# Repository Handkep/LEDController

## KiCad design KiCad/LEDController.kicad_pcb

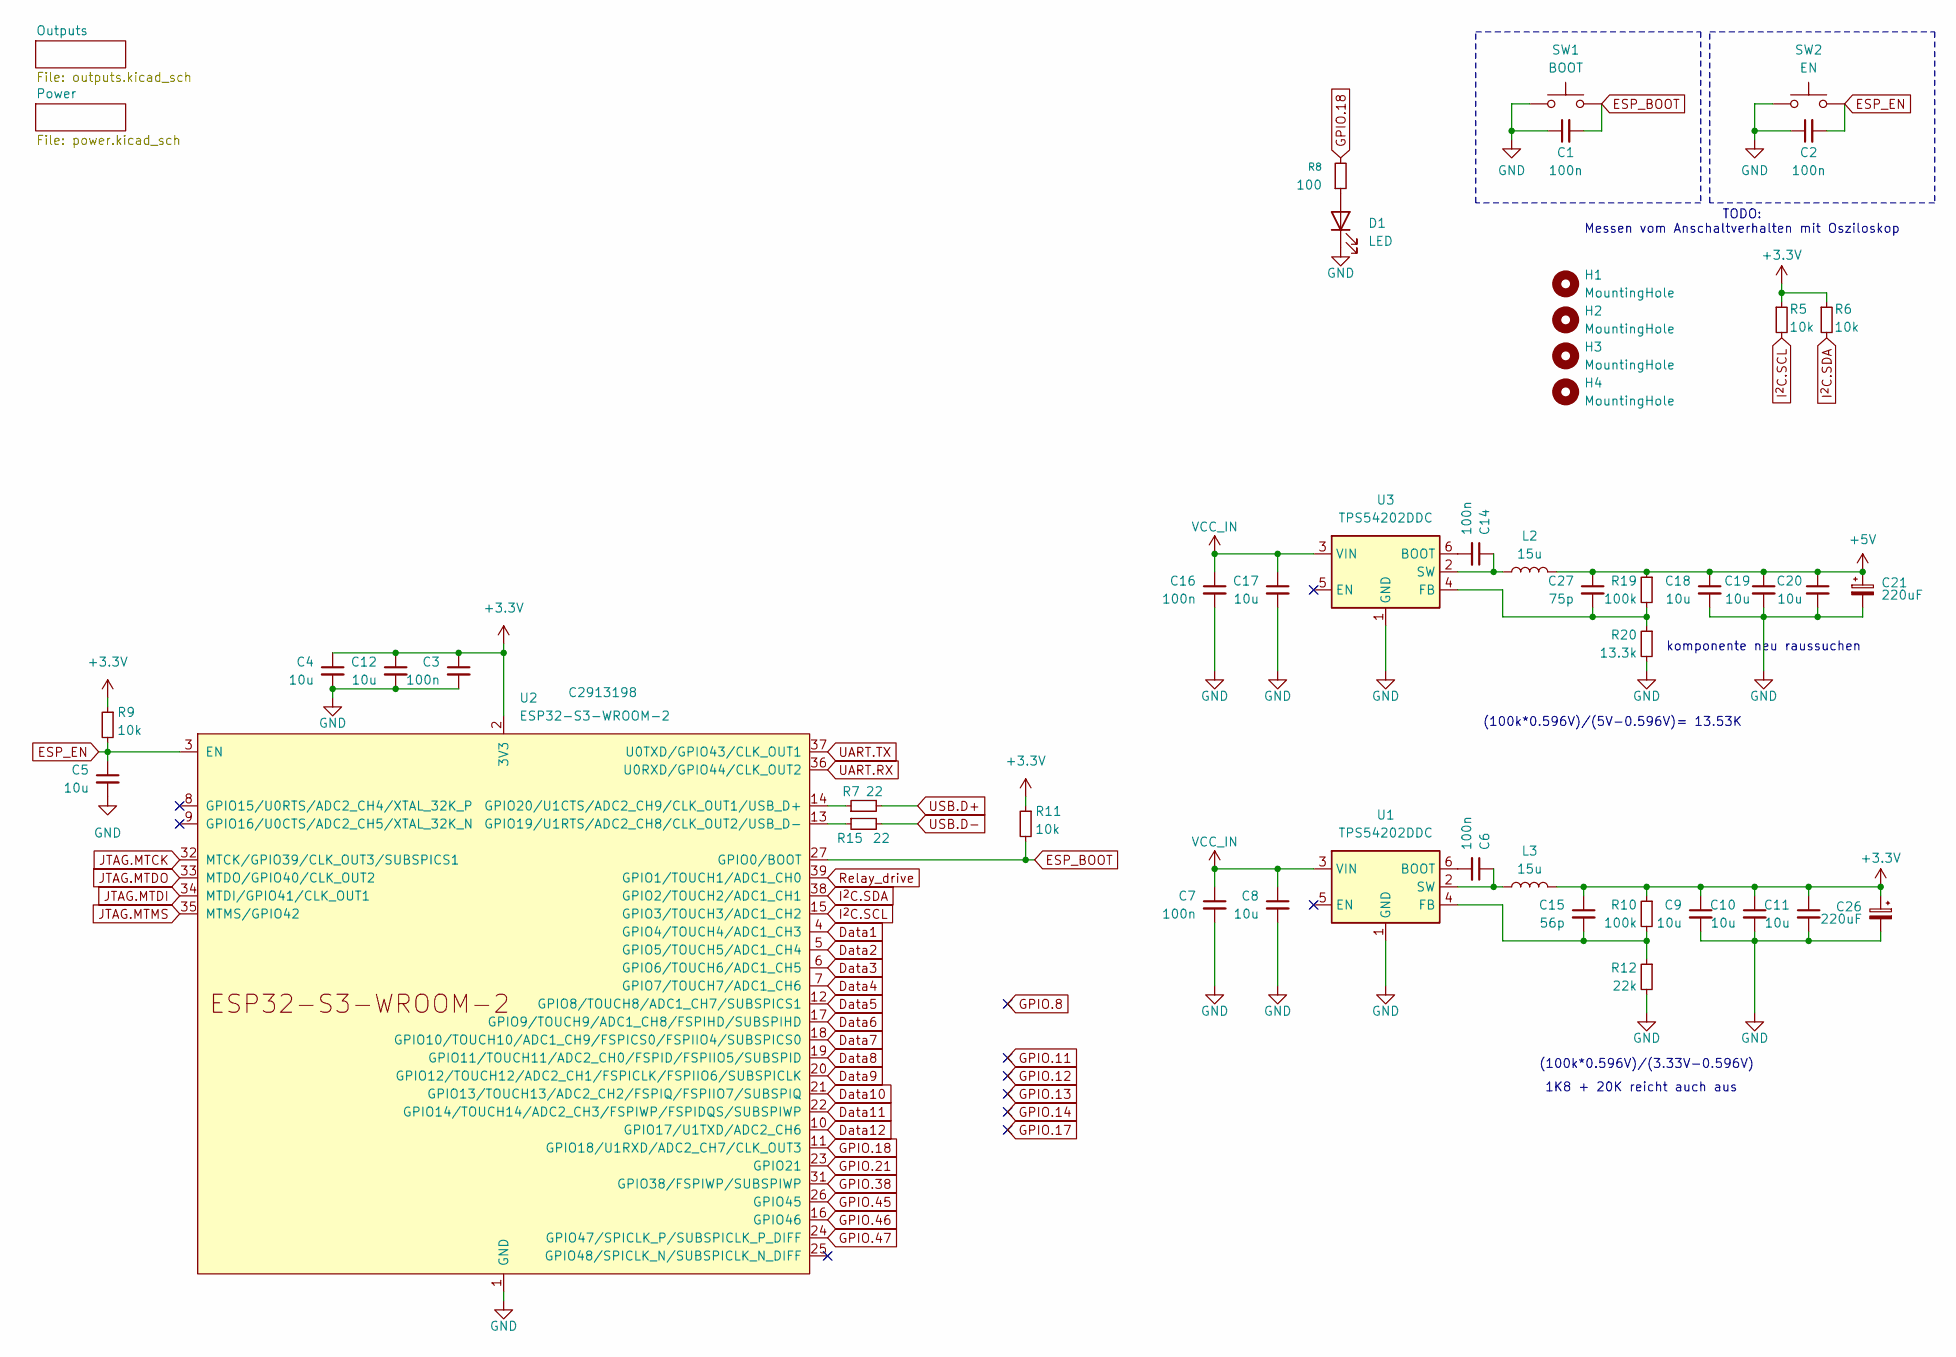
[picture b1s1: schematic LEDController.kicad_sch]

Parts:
C1, C2, C3, C6, C7, C14, C16: 100n; C_0805_2012Metric_Pad1.18x1.45mm_HandSolder; LCSC C5137467
C4, C5, C8, C9, C10, C11, C12, C17, C18, C19, C20: 10u; C_0805_2012Metric_Pad1.18x1.45mm_HandSolder; LCSC C33546007
C15: 56p; C_0805_2012Metric_Pad1.18x1.45mm_HandSolder
C21, C26: 220uF; CP_Radial_D8.0mm_P3.50mm; LCSC C107639
C27: 75p; C_0805_2012Metric_Pad1.18x1.45mm_HandSolder
D1: LED; LED_0603_1608Metric_Pad1.05x0.95mm_HandSolder; LCSC C7496818
H1, H2, H3, H4: MountingHole; MountingHole_3.2mm_M3
L2, L3: 15u; L_APV_APH0630; LCSC C5349699
R5, R6, R9, R11: 10k; R_0805_2012Metric_Pad1.20x1.40mm_HandSolder; LCSC C2930231
R7, R15: 22; R_0805_2012Metric_Pad1.20x1.40mm_HandSolder
R8: 100; R_0805_2012Metric_Pad1.20x1.40mm_HandSolder; LCSC C2907294
R10, R19: 100k; R_0805_2012Metric_Pad1.20x1.40mm_HandSolder; LCSC C3017875
R12: 22k; R_0805_2012Metric_Pad1.20x1.40mm_HandSolder; LCSC C2907015
R20: 13.3k; R_0805_2012Metric_Pad1.20x1.40mm_HandSolder; LCSC C3017875
SW1: BOOT; SHOU HAN TS342A2P-WZ; LCSC C557591
SW2: EN; SHOU HAN TS342A2P-WZ; LCSC C557591
U1, U3: TPS54202DDC; SOT-23-6; LCSC C191884
U2: ESP32-S3-WROOM-2; LCSC C2913198

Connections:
+3.3V: C3.1, C4.1, C9.1, C10.1, C11.1, C12.1, C15.1, C26.1, L3.2, R5.1, R6.1, R9.1, R10.1, R11.1, U2.2 (3V3); also elsewhere on the board
+5V: C18.1, C19.1, C20.1, C21.1, C27.1, L2.2, R19.1; also elsewhere on the board
Data1: U2.4 (GPIO4/TOUCH4/ADC1_CH3); also elsewhere on the board
Data2: U2.5 (GPIO5/TOUCH5/ADC1_CH4); also elsewhere on the board
Data3: U2.6 (GPIO6/TOUCH6/ADC1_CH5); also elsewhere on the board
Data4: U2.7 (GPIO7/TOUCH7/ADC1_CH6); also elsewhere on the board
Data5: U2.12 (GPIO8/TOUCH8/ADC1_CH7/SUBSPICS1); also elsewhere on the board
Data6: U2.17 (GPIO9/TOUCH9/ADC1_CH8/FSPIHD/SUBSPIHD); also elsewhere on the board
Data7: U2.18 (GPIO10/TOUCH10/ADC1_CH9/FSPICS0/FSPIIO4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); also elsewhere on the board
Data8: U2.19 (GPIO11/TOUCH11/ADC2_CH0/FSPID/FSPIIO5/S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); also elsewhere on the board
Data9: U2.20 (GPIO12/TOUCH12/ADC2_CH1/FSPICLK/FSPIIO6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); also elsewhere on the board
Data10: U2.21 (GPIO13/TOUCH13/ADC2_CH2/FSPIQ/FSPIIO7/S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); also elsewhere on the board
Data11: U2.22 (GPIO14/TOUCH14/ADC2_CH3/FSPIWP/FSPIDQS/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)
Data12: U2.10 (GPIO17/U1TXD/ADC2_CH6)
ESP_BOOT: C1.2, R11.2, SW1.2, U2.27 (GPIO0/BOOT)
ESP_EN: C2.2, C5.1, R9.2, SW2.2, U2.3 (EN)
GND: C1.1, C2.1, C3.2, C4.2, C5.2, C7.2, C8.2, C9.2, C10.2, C11.2, C12.2, C16.2, C17.2, C18.2, C19.2, C20.2, C21.2, C26.2, D1.1 (K), R12.2, R20.2, SW1.1, SW2.1, U1.1 (GND), U2.1 (GND), U2.40 (GND), U2.41 (GND), U3.1 (GND); also elsewhere on the board
GPIO.18: R8.2, U2.11 (GPIO18/U1RXD/ADC2_CH7/CLK_OUT3); also elsewhere on the board
GPIO.21: U2.23 (GPIO21); also elsewhere on the board
GPIO.38: U2.31 (GPIO38/FSPIWP/SUBSPIWP); also elsewhere on the board
GPIO.45: U2.26 (GPIO45); also elsewhere on the board
GPIO.46: U2.16 (GPIO46); also elsewhere on the board
GPIO.47: U2.24 (GPIO47/SPICLK_P/SUBSPICLK_P_DIFF); also elsewhere on the board
I^{2}C.SCL: R5.2, U2.15 (GPIO3/TOUCH3/ADC1_CH2)
I^{2}C.SDA: R6.2, U2.38 (GPIO2/TOUCH2/ADC1_CH1)
JTAG.MTCK: U2.32 (MTCK/GPIO39/CLK_OUT3/SUBSPICS1); also elsewhere on the board
JTAG.MTDI: U2.34 (MTDI/GPIO41/CLK_OUT1); also elsewhere on the board
JTAG.MTDO: U2.33 (MTDO/GPIO40/CLK_OUT2); also elsewhere on the board
JTAG.MTMS: U2.35 (MTMS/GPIO42); also elsewhere on the board
unnamed: D1.2 (A), R8.1
unnamed: C6.2, U1.6 (BOOT)
unnamed: C15.2, R10.2, R12.1, U1.4 (FB)
unnamed: C6.1, L3.1, U1.2 (SW)
unnamed: R15.1, U2.13 (GPIO19/U1RTS/ADC2_CH8/CLK_OUT2/USB_D-)
unnamed: R7.1, U2.14 (GPIO20/U1CTS/ADC2_CH9/CLK_OUT1/USB_D+)
unnamed: C14.2, U3.6 (BOOT)
unnamed: C27.2, R19.2, R20.1, U3.4 (FB)
unnamed: C14.1, L2.1, U3.2 (SW)
Relay_drive: U2.39 (GPIO1/TOUCH1/ADC1_CH0); also elsewhere on the board
UART.RX: U2.36 (U0RXD/GPIO44/CLK_OUT2); also elsewhere on the board
UART.TX: U2.37 (U0TXD/GPIO43/CLK_OUT1); also elsewhere on the board
USB.D+: R7.2; also elsewhere on the board
USB.D-: R15.2; also elsewhere on the board
VCC_IN: C7.1, C8.1, C16.1, C17.1, U1.3 (VIN), U3.3 (VIN); also elsewhere on the board

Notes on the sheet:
(100k*0.596V)/(5V-0.596V)= 13.53K
komponente neu raussuchen
(100k*0.596V)/(3.33V-0.596V)
1K8 + 20K reicht auch aus
TODO: Messen vom Anschaltverhalten mit Osziloskop

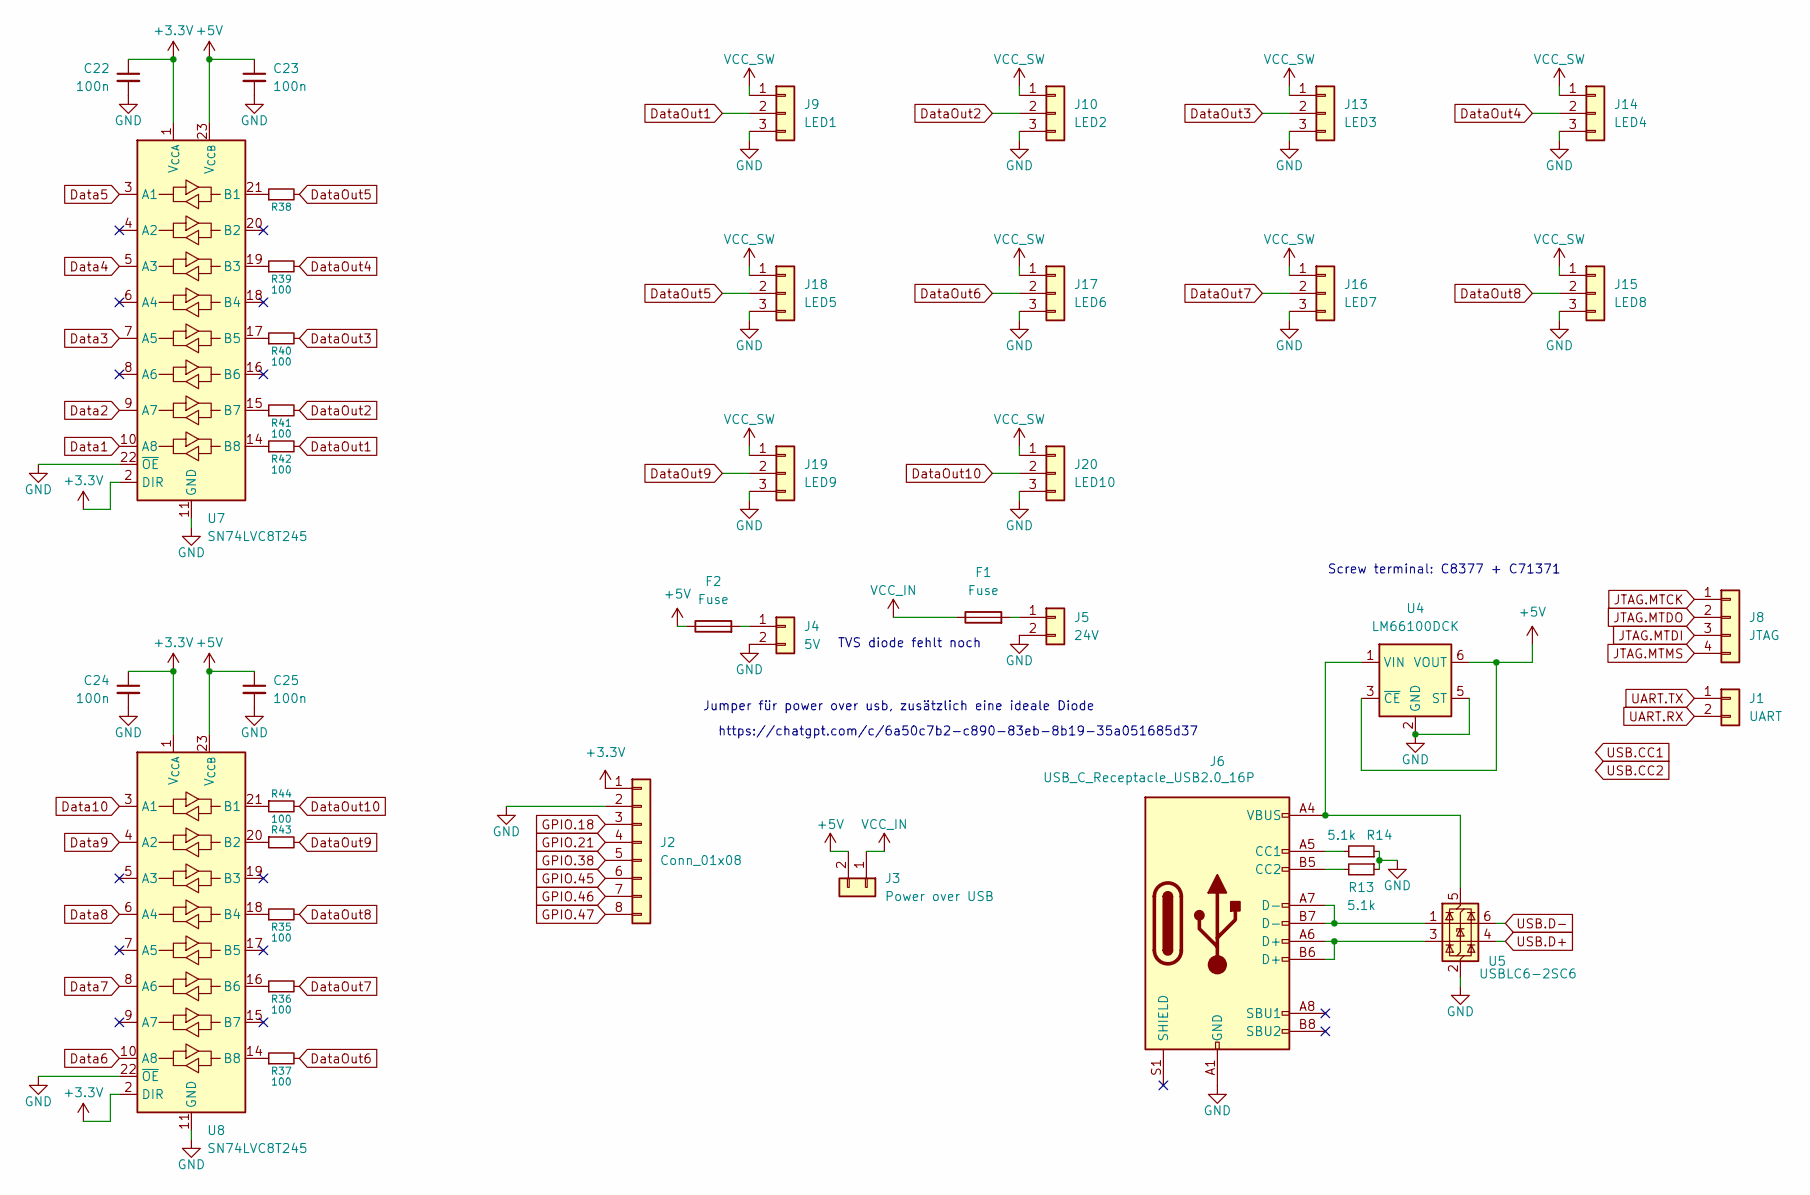
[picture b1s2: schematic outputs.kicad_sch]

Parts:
C22, C23, C24, C25: 100n; C_0805_2012Metric_Pad1.18x1.45mm_HandSolder; LCSC C5137467
F1, F2: Fuse; Fuseholder_Blade_Mini_Keystone_3568; LCSC C19727305
J1: UART; PinHeader_1x02_P2.54mm_Vertical
J2: Conn_01x08; PinHeader_1x08_P2.54mm_Vertical
J3: Power over USB; PinHeader_1x02_P2.54mm_Vertical
J4: 5V; CONN-TH_HB9500M-9.5-2P; LCSC C601239
J5: 24V; CONN-TH_HB9500M-9.5-2P; LCSC C601239
J6: USB_C_Receptacle_USB2.0_16P; USB_C_Receptacle_GCT_USB4105-xx-A_16P_TopMnt_Horizontal; LCSC C2765186
J8: JTAG; PinHeader_1x04_P2.54mm_Vertical
J9: LED1; CONN-TH_3P-P5.08_WJ2EDGRC-5.08-3P; LCSC C8377
J10: LED2; CONN-TH_3P-P5.08_WJ2EDGRC-5.08-3P; LCSC C8377
J13: LED3; CONN-TH_3P-P5.08_WJ2EDGRC-5.08-3P; LCSC C8377
J14: LED4; CONN-TH_3P-P5.08_WJ2EDGRC-5.08-3P; LCSC C8377
J15: LED8; CONN-TH_3P-P5.08_WJ2EDGRC-5.08-3P; LCSC C8377
J16: LED7; CONN-TH_3P-P5.08_WJ2EDGRC-5.08-3P; LCSC C8377
J17: LED6; CONN-TH_3P-P5.08_WJ2EDGRC-5.08-3P; LCSC C8377
J18: LED5; CONN-TH_3P-P5.08_WJ2EDGRC-5.08-3P; LCSC C8377
J19: LED9; CONN-TH_3P-P5.08_WJ2EDGRC-5.08-3P; LCSC C8377
J20: LED10; CONN-TH_3P-P5.08_WJ2EDGRC-5.08-3P; LCSC C8377
R13, R14: 5.1k; R_0805_2012Metric_Pad1.20x1.40mm_HandSolder; LCSC C2930296
R35, R36, R37, R38, R39, R40, R41, R42, R43, R44: 100; R_0805_2012Metric_Pad1.20x1.40mm_HandSolder; LCSC C2907294
U4: LM66100DCK; SOT-363_SC-70-6; LCSC C2869734
U5: USBLC6-2SC6; SOT-23-6; LCSC C21713975
U7, U8: SN74LVC8T245; TSSOP-24_4.4x7.8mm_P0.65mm; LCSC C27643

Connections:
+3.3V: C22.1, C24.1, J2.1, U7.1 (V_{CCA}), U7.2 (DIR), U8.1 (V_{CCA}), U8.2 (DIR); also elsewhere on the board
+5V: C23.1, C25.1, F2.1, J3.2, U4.3 (~CE), U4.6 (VOUT), U7.23 (V_{CCB}), U7.24 (V_{CCB}), U8.23 (V_{CCB}), U8.24 (V_{CCB}); also elsewhere on the board
Data1: U7.10 (A8); also elsewhere on the board
Data2: U7.9 (A7); also elsewhere on the board
Data3: U7.7 (A5); also elsewhere on the board
Data4: U7.5 (A3); also elsewhere on the board
Data5: U7.3 (A1); also elsewhere on the board
Data6: U8.10 (A8); also elsewhere on the board
Data7: U8.8 (A6); also elsewhere on the board
Data8: U8.6 (A4); also elsewhere on the board
Data9: U8.4 (A2); also elsewhere on the board
Data10: U8.3 (A1); also elsewhere on the board
DataOut1: J9.2, R42.2
DataOut2: J10.2, R41.2
DataOut3: J13.2, R40.2
DataOut4: J14.2, R39.2
DataOut5: J18.2, R38.2
DataOut6: J17.2, R37.2
DataOut7: J16.2, R36.2
DataOut8: J15.2, R35.2
DataOut9: J19.2, R43.2
DataOut10: J20.2, R44.2
GND: C22.2, C23.2, C24.2, C25.2, J2.2, J4.2, J5.2, J6.A1 (GND), J6.A12 (GND), J6.B1 (GND), J6.B12 (GND), J9.3, J10.3, J13.3, J14.3, J15.3, J16.3, J17.3, J18.3, J19.3, J20.3, R13.1, R14.1, U4.2 (GND), U4.5 (ST), U5.2 (GND), U7.11 (GND), U7.12 (GND), U7.13 (GND), U7.22 (~OE), U8.11 (GND), U8.12 (GND), U8.13 (GND), U8.22 (~OE); also elsewhere on the board
GPIO.18: J2.3; also elsewhere on the board
GPIO.21: J2.4; also elsewhere on the board
GPIO.38: J2.5; also elsewhere on the board
GPIO.45: J2.6; also elsewhere on the board
GPIO.46: J2.7; also elsewhere on the board
GPIO.47: J2.8; also elsewhere on the board
JTAG.MTCK: J8.1; also elsewhere on the board
JTAG.MTDI: J8.3; also elsewhere on the board
JTAG.MTDO: J8.2; also elsewhere on the board
JTAG.MTMS: J8.4; also elsewhere on the board
unnamed: F2.2, J4.1
unnamed: F1.2, J5.1
unnamed: J6.A5 (CC1), R14.2
unnamed: J6.B5 (CC2), R13.2
unnamed: J6.A6 (D+), J6.B6 (D+), U5.3 (I/O2)
unnamed: J6.A7 (D-), J6.B7 (D-), U5.1 (I/O1)
unnamed: J6.A4 (VBUS), J6.A9 (VBUS), J6.B4 (VBUS), J6.B9 (VBUS), U4.1 (VIN), U5.5 (VBUS)
unnamed: R38.1, U7.21 (B1)
unnamed: R39.1, U7.19 (B3)
unnamed: R40.1, U7.17 (B5)
unnamed: R41.1, U7.15 (B7)
unnamed: R42.1, U7.14 (B8)
unnamed: R44.1, U8.21 (B1)
unnamed: R43.1, U8.20 (B2)
unnamed: R35.1, U8.18 (B4)
unnamed: R36.1, U8.16 (B6)
unnamed: R37.1, U8.14 (B8)
UART.RX: J1.2; also elsewhere on the board
UART.TX: J1.1; also elsewhere on the board
USB.D+: U5.4 (I/O2); also elsewhere on the board
USB.D-: U5.6 (I/O1); also elsewhere on the board
VCC_IN: F1.1, J3.1; also elsewhere on the board
VCC_SW: J9.1, J10.1, J13.1, J14.1, J15.1, J16.1, J17.1, J18.1, J19.1, J20.1; also elsewhere on the board

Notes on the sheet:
TVS diode fehlt noch
https://chatgpt.com/c/6a50c7b2-c890-83eb-8b19-35a051685d37
Jumper für power over usb, zusätzlich eine ideale Diode
Screw terminal: C8377 + C71371

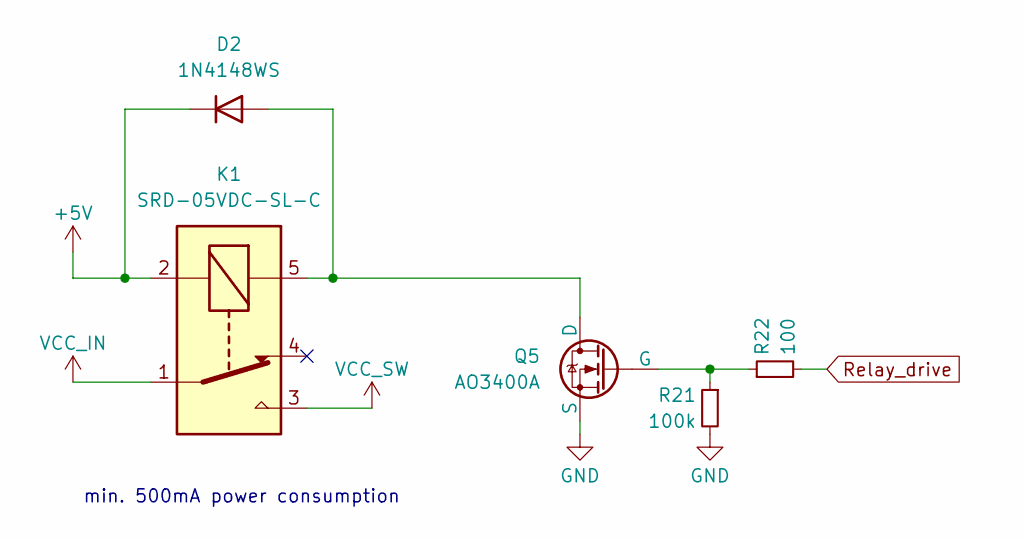
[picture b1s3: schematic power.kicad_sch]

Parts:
D2: 1N4148WS; D_SOD-323; LCSC C917030
K1: SRD-05VDC-SL-C; Relay_SPDT_SANYOU_SRD_Series_Form_C; LCSC C35449
Q5: AO3400A; SOT-23; LCSC C20917
R21: 100k; R_0805_2012Metric_Pad1.20x1.40mm_HandSolder; LCSC C3017875
R22: 100; R_0805_2012Metric_Pad1.20x1.40mm_HandSolder; LCSC C2907294

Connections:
+5V: D2.1 (K), K1.2; also elsewhere on the board
GND: Q5.3 (S), R21.2; also elsewhere on the board
unnamed: D2.2 (A), K1.5, Q5.1 (D)
unnamed: Q5.2 (G), R21.1, R22.1
Relay_drive: R22.2; also elsewhere on the board
VCC_IN: K1.1; also elsewhere on the board
VCC_SW: K1.3; also elsewhere on the board

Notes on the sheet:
min. 500mA power consumption

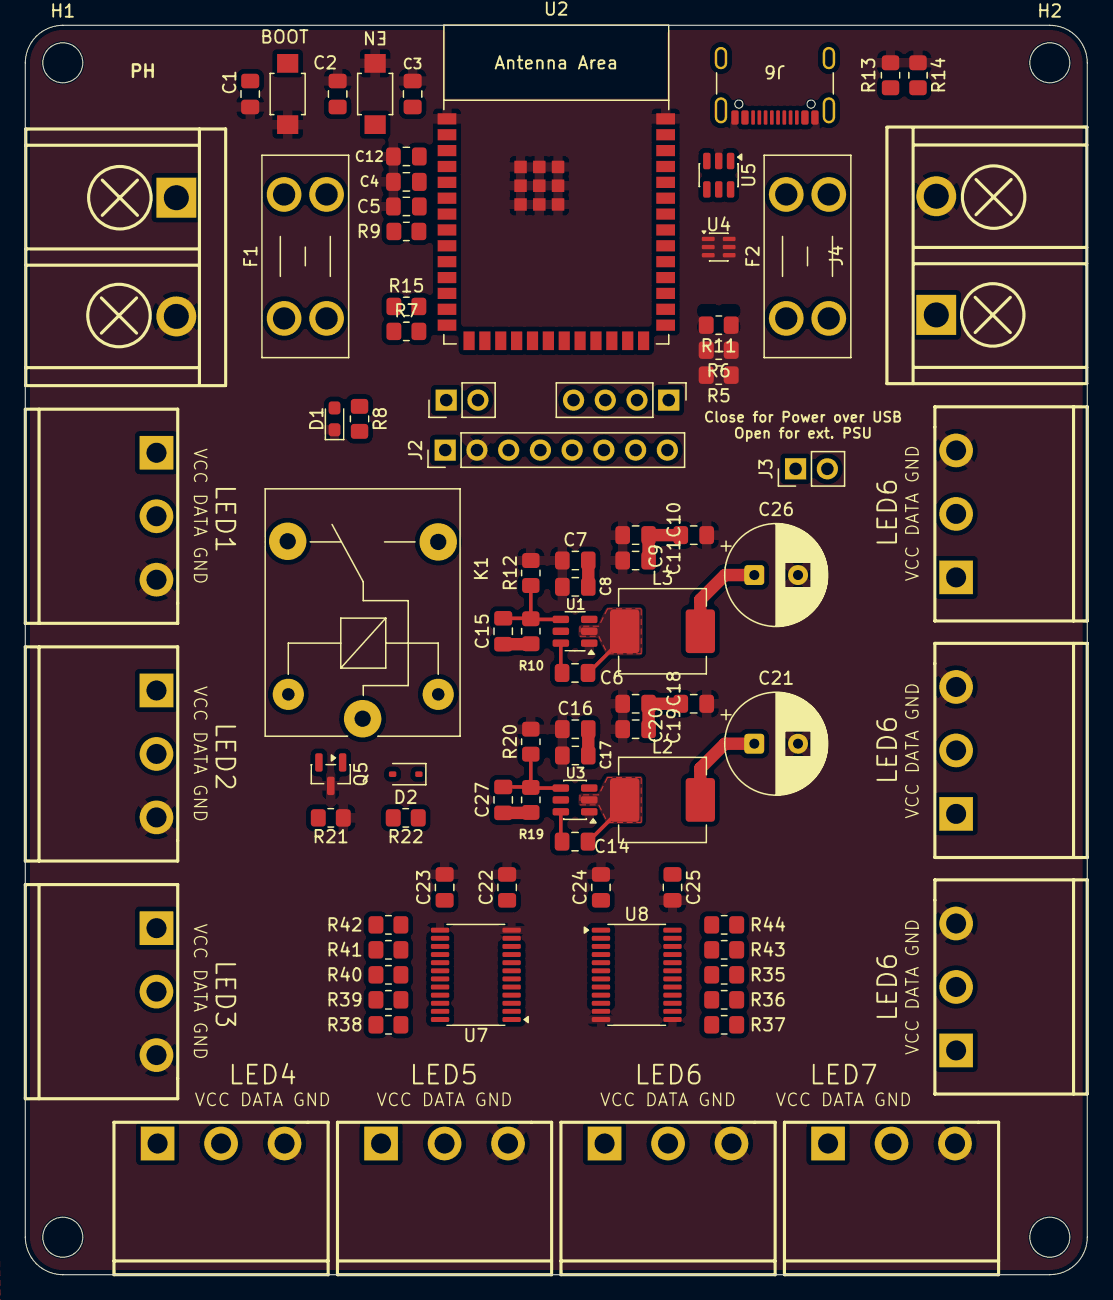
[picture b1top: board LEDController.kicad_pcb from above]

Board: 4 copper layers, 85.0 x 100.0 mm, 89 parts (0 on the bottom side), 72 nets.

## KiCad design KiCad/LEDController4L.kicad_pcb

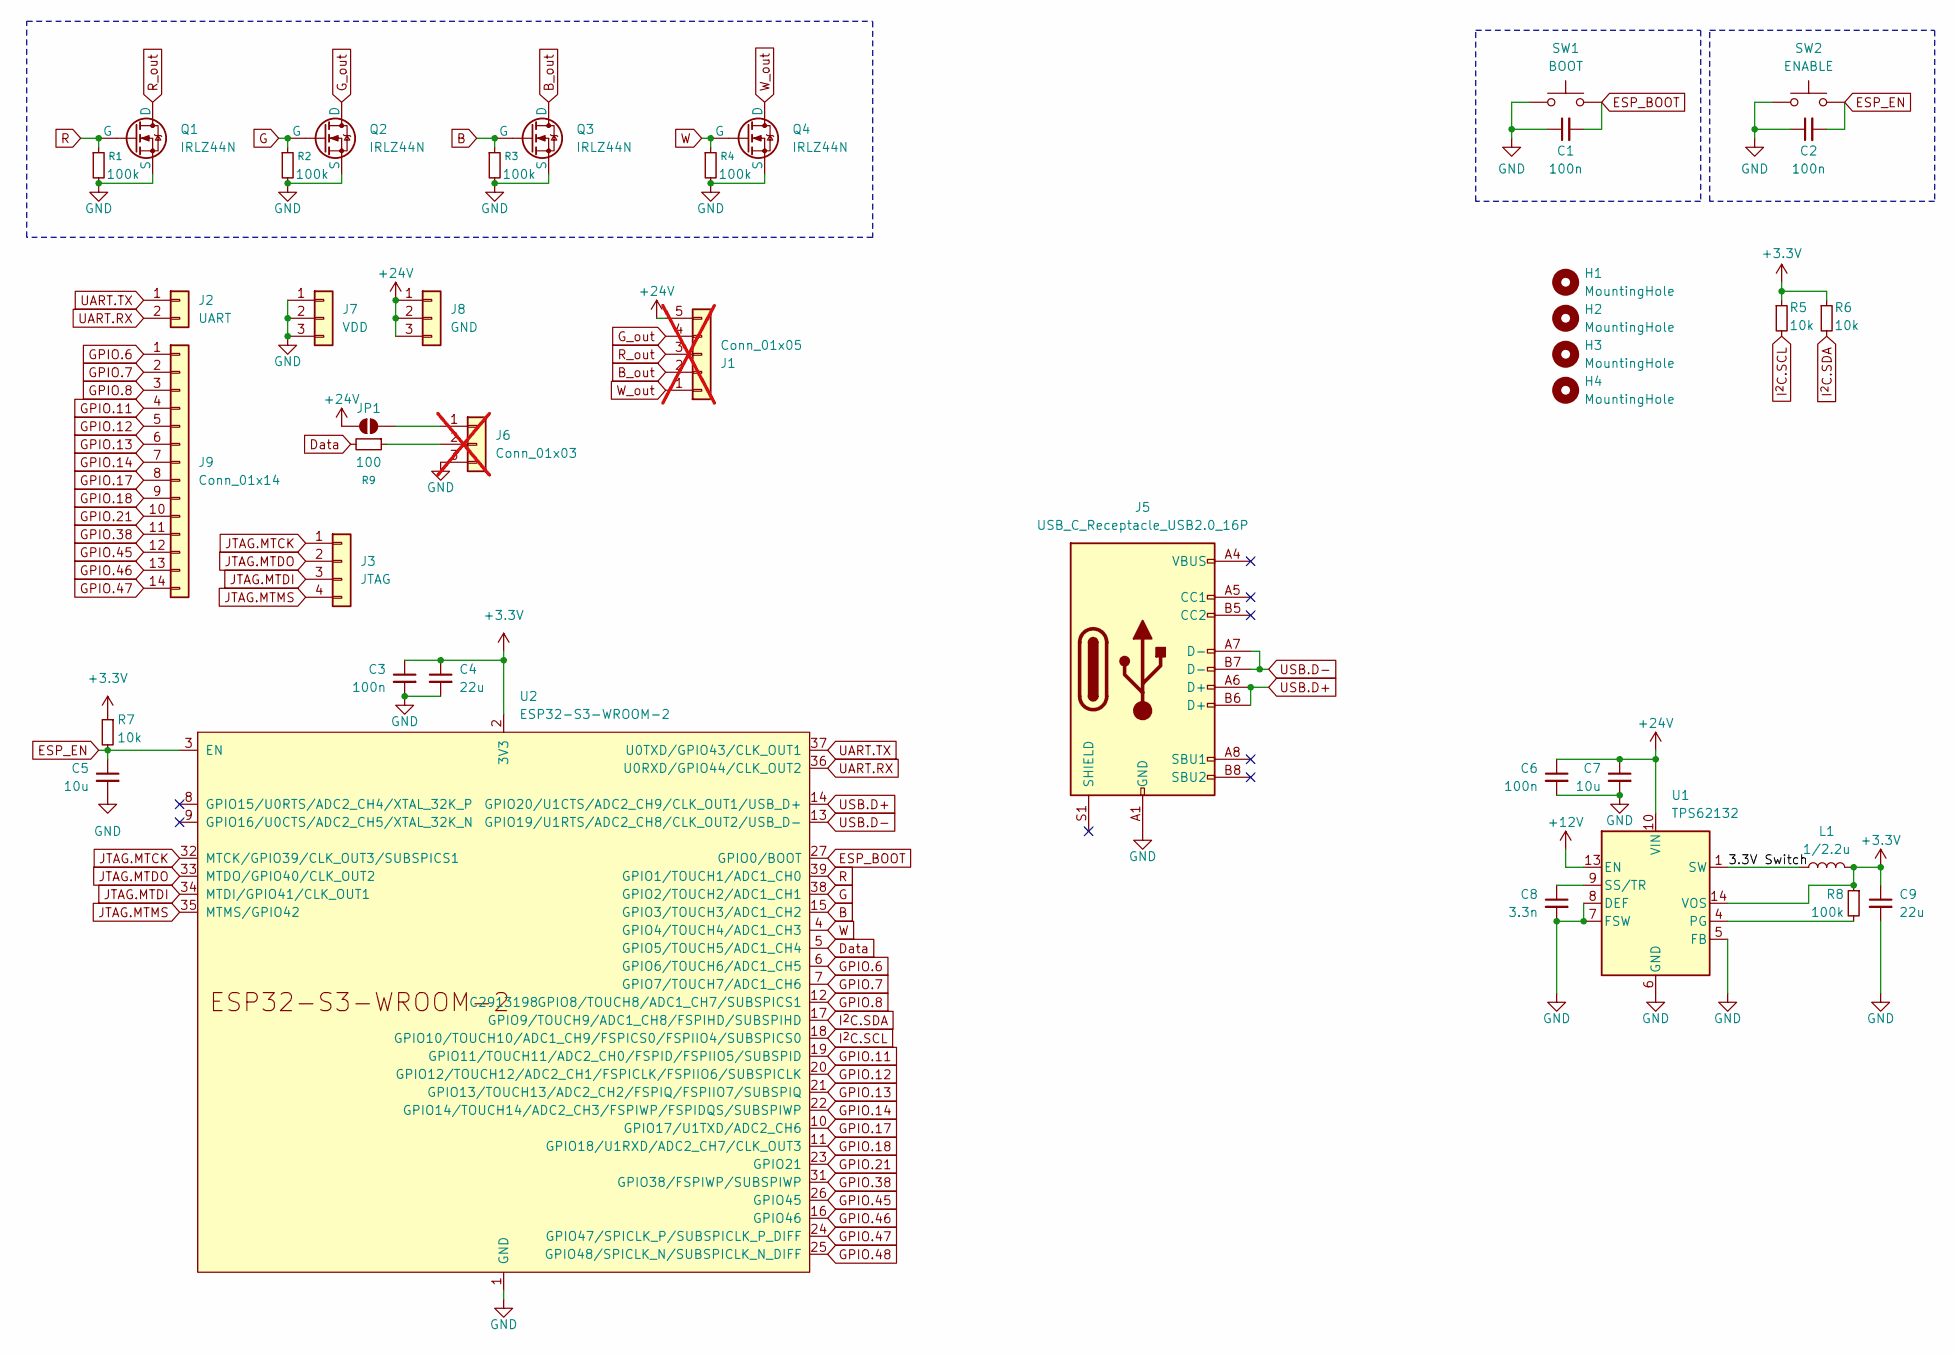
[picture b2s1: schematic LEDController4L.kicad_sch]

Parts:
C1, C2, C3, C6: 100n; C_0805_2012Metric_Pad1.18x1.45mm_HandSolder
C4, C9: 22u; C_0805_2012Metric_Pad1.18x1.45mm_HandSolder
C5, C7: 10u; C_1210_3225Metric_Pad1.33x2.70mm_HandSolder
C8: 3.3n; C_0805_2012Metric_Pad1.18x1.45mm_HandSolder
H1, H2, H3, H4: MountingHole; MountingHole_3.2mm_M3
J1: Conn_01x05; JST_XH_B5B-XH-A_1x05_P2.50mm_Vertical; not fitted
J2: UART; PinHeader_1x02_P2.54mm_Vertical
J3: JTAG; PinHeader_1x04_P2.54mm_Vertical
J5: USB_C_Receptacle_USB2.0_16P; USB_C_Receptacle_GCT_USB4105-xx-A_16P_TopMnt_Horizontal; LCSC C2765186
J6: Conn_01x03; JST_XH_B3B-XH-A_1x03_P2.50mm_Vertical; not fitted
J7: VDD; TerminalBlock_Phoenix_MKDS-1,5-3-5.08_1x03_P5.08mm_Horizont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
J8: GND; TerminalBlock_Phoenix_MKDS-1,5-3-5.08_1x03_P5.08mm_Horizont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
J9: Conn_01x14; PinHeader_1x14_P2.54mm_Vertical
JP1: SolderJumper_2_Open; SolderJumper-2_P1.3mm_Open_RoundedPad1.0x1.5mm
L1: 1/2.2u; L_APV_ANR4026
Q1, Q2, Q3, Q4: IRLZ44N; TO-220-3_Vertical; LCSC C42370423
R1, R2, R3, R4, R8: 100k; R_0805_2012Metric_Pad1.20x1.40mm_HandSolder; LCSC C3017875
R5, R6, R7: 10k; R_0805_2012Metric_Pad1.20x1.40mm_HandSolder; LCSC C2930231
R9: 100; R_0805_2012Metric_Pad1.20x1.40mm_HandSolder; LCSC C2907294
SW1: BOOT; SHOU HAN TS342A2P-WZ; LCSC C557591
SW2: ENABLE; SHOU HAN TS342A2P-WZ; LCSC C557591
U1: TPS62132; VQFN-16-1EP_3x3mm_P0.5mm_EP1.68x1.68mm_ThermalVias; LCSC C81563
U2: ESP32-S3-WROOM-2; LCSC C2913198

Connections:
+3.3V: C3.1, C4.1, C9.1, L1.2, R5.1, R6.1, R7.1, R8.1, U1.14 (VOS), U2.2 (3V3)
+12V: U1.13 (EN)
+24V: C6.1, C7.1, J1.5, J8.1, J8.2, J8.3, JP1.1 (A), U1.10 (VIN), U1.11 (VIN), U1.12 (VIN)
/3.3V Switch: L1.1, U1.1 (SW), U1.2 (SW), U1.3 (SW)
B: Q3.2 (G), R3.1, U2.15 (GPIO3/TOUCH3/ADC1_CH2)
B_out: J1.2, Q3.1 (D)
Data: R9.2, U2.5 (GPIO5/TOUCH5/ADC1_CH4)
ESP_BOOT: C1.2, SW1.2, U2.27 (GPIO0/BOOT)
ESP_EN: C2.2, C5.1, R7.2, SW2.2, U2.3 (EN)
G: Q2.2 (G), R2.1, U2.38 (GPIO2/TOUCH2/ADC1_CH1)
GND: C1.1, C2.1, C3.2, C4.2, C5.2, C6.2, C7.2, C8.2, C9.2, J5.A1 (GND), J5.A12 (GND), J5.B1 (GND), J5.B12 (GND), J6.3, J7.1, J7.2, J7.3, Q1.3 (S), Q2.3 (S), Q3.3 (S), Q4.3 (S), R1.2, R2.2, R3.2, R4.2, SW1.1, SW2.1, U1.5 (FB), U1.6 (GND), U1.7 (FSW), U1.8 (DEF), U1.15 (GND), U1.16 (GND), U1.17 (GND), U2.1 (GND), U2.40 (GND), U2.41 (GND)
GPIO.6: J9.1, U2.6 (GPIO6/TOUCH6/ADC1_CH5)
GPIO.7: J9.2, U2.7 (GPIO7/TOUCH7/ADC1_CH6)
GPIO.8: J9.3, U2.12 (GPIO8/TOUCH8/ADC1_CH7/SUBSPICS1)
GPIO.11: J9.4, U2.19 (GPIO11/TOUCH11/ADC2_CH0/FSPID/FSPIIO5/S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)
GPIO.12: J9.5, U2.20 (GPIO12/TOUCH12/ADC2_CH1/FSPICLK/FSPIIO6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)
GPIO.13: J9.6, U2.21 (GPIO13/TOUCH13/ADC2_CH2/FSPIQ/FSPIIO7/S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)
GPIO.14: J9.7, U2.22 (GPIO14/TOUCH14/ADC2_CH3/FSPIWP/FSPIDQS/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)
GPIO.17: J9.8, U2.10 (GPIO17/U1TXD/ADC2_CH6)
GPIO.18: J9.9, U2.11 (GPIO18/U1RXD/ADC2_CH7/CLK_OUT3)
GPIO.21: J9.10, U2.23 (GPIO21)
GPIO.38: J9.11, U2.31 (GPIO38/FSPIWP/SUBSPIWP)
GPIO.45: J9.12, U2.26 (GPIO45)
GPIO.46: J9.13, U2.16 (GPIO46)
GPIO.47: J9.14, U2.24 (GPIO47/SPICLK_P/SUBSPICLK_P_DIFF)
GPIO.48: U2.25 (GPIO48/SPICLK_N/SUBSPICLK_N_DIFF)
G_out: J1.4, Q2.1 (D)
I^{2}C.SCL: R5.2, U2.18 (GPIO10/TOUCH10/ADC1_CH9/FSPICS0/FSPIIO4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)
I^{2}C.SDA: R6.2, U2.17 (GPIO9/TOUCH9/ADC1_CH8/FSPIHD/SUBSPIHD)
JTAG.MTCK: J3.1, U2.32 (MTCK/GPIO39/CLK_OUT3/SUBSPICS1)
JTAG.MTDI: J3.3, U2.34 (MTDI/GPIO41/CLK_OUT1)
JTAG.MTDO: J3.2, U2.33 (MTDO/GPIO40/CLK_OUT2)
JTAG.MTMS: J3.4, U2.35 (MTMS/GPIO42)
unnamed: J6.1, JP1.2 (B)
unnamed: J6.2, R9.1
unnamed: R8.2, U1.4 (PG)
unnamed: C8.1, U1.9 (SS/TR)
R: Q1.2 (G), R1.1, U2.39 (GPIO1/TOUCH1/ADC1_CH0)
R_out: J1.3, Q1.1 (D)
UART.RX: J2.2, U2.36 (U0RXD/GPIO44/CLK_OUT2)
UART.TX: J2.1, U2.37 (U0TXD/GPIO43/CLK_OUT1)
USB.D+: J5.A6 (D+), J5.B6 (D+), U2.14 (GPIO20/U1CTS/ADC2_CH9/CLK_OUT1/USB_D+)
USB.D-: J5.A7 (D-), J5.B7 (D-), U2.13 (GPIO19/U1RTS/ADC2_CH8/CLK_OUT2/USB_D-)
W: Q4.2 (G), R4.1, U2.4 (GPIO4/TOUCH4/ADC1_CH3)
W_out: J1.1, Q4.1 (D)

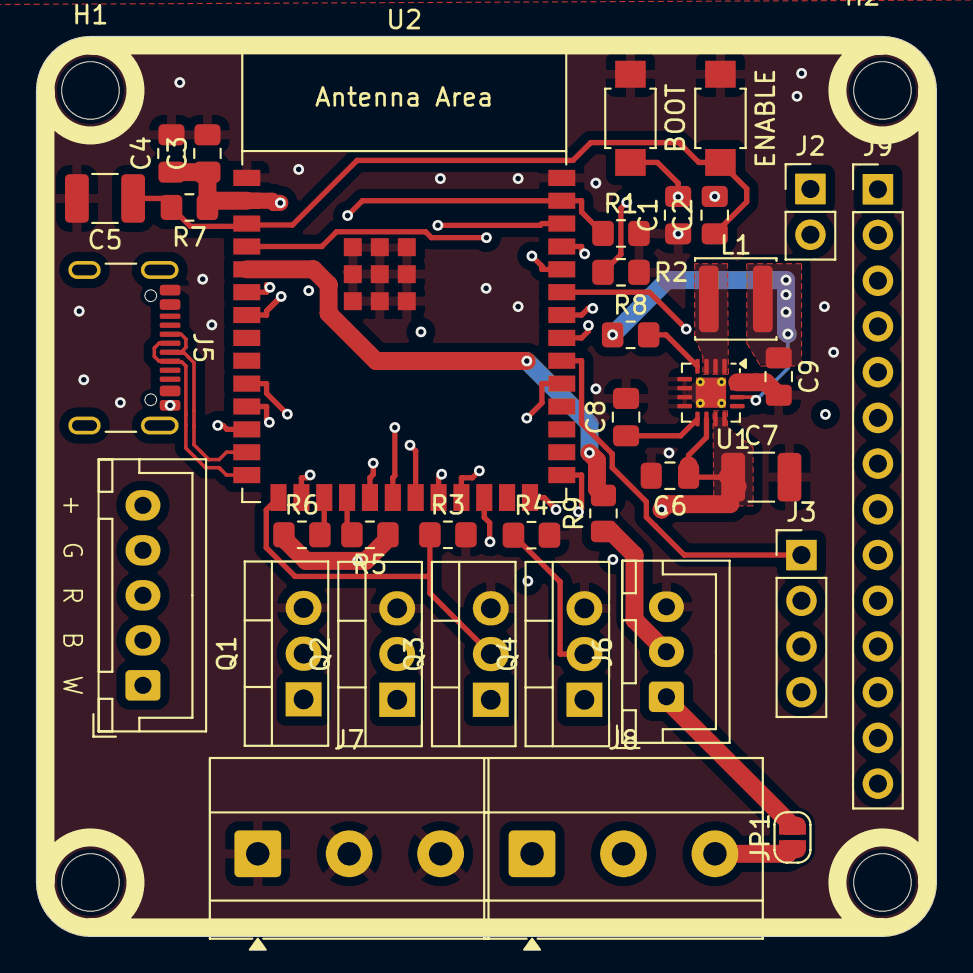
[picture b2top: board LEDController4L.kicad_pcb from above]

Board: 4 copper layers, 50.0 x 50.0 mm, 40 parts (0 on the bottom side), 43 nets.

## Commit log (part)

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2025-05-26 place components
2025-05-26 start routing
2025-05-26 add aditional header
2025-05-26 autoroute
2025-05-27 add kikit board2pdf, add some headers, route
2025-05-27 route
2025-05-27 convert to 4 layer pcb
2025-05-27 add different buck converter
2025-05-30 rearrange again, route
2025-05-30 add led
2025-06-03 jlcpcb order
2025-09-28 add mains power
2026-01-16 add 5v buck converter
2026-06-03 initial design document
2026-06-05 change prototype
2026-06-05 add relay
2026-06-10 add lcsc numbers
2026-06-11 work on new design
2026-06-11 work
2026-06-17 arrange components
2026-06-18 init agents, change schematic
